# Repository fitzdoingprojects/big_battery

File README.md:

# big_battery
Charge Controller for 12 cell Lifepo4 batteries

Output voltage can be adjusted between 0 and 110% with voltage between TRM and -S on CN1:
Output Voltage = (Voltage between TMR and -S / 2.5) * 5V

Output current can be measured between CB adn -S on either CN1 or CN2.
Ouput current: 1Vcb = 0A, 0Vcb = 50A, -1Vcb = 100A
	Iout = 50 * (-Vcb + 1)
Required input impedance > 500kOh
Max current 120A ???

Circuit:
	Set TRM to default ouput of 4.2V, allow output range of 0 to 4.2V
	Invert and shift current sense from -1 to 2V, to 0V to 2.4V
	Over current feedback, with max current and trickle current
	Isolated signalling, either capacitive or dedicated IC

TESTING:
	* Double check default output voltage of 4.2V
	* Double check current graph/equation

Results:
    With 0 current, CB measuers 1.221V
    1A , 1.5V
    2A, 1.13
	3A, 1.098
	4A, 1.069
	5A, 1.04
SHOULD REQUIRE DIRECT TURN OFF?

BOARD REVISION:
 * ADD 3.3V test point
 * ADD potentiometer for adjusting current and voltage set points
 * change plus and minus inputs on op-amp B (because CB voltage decreases as voltage rises)
 * add reverse input protection diode
 * make sure trickle disable is pulled low
 * add some leds for signalling

 HOW FLASH EFM8 MCU:
 
 https://www.silabs.com/community/mcu/8-bit/knowledge-base.entry.html/2015/06/08/how_to_use_efm8_star-8aHu
 https://www.allaboutcircuits.com/projects/custom-pcb-design-with-an-efm8-microcontroller/

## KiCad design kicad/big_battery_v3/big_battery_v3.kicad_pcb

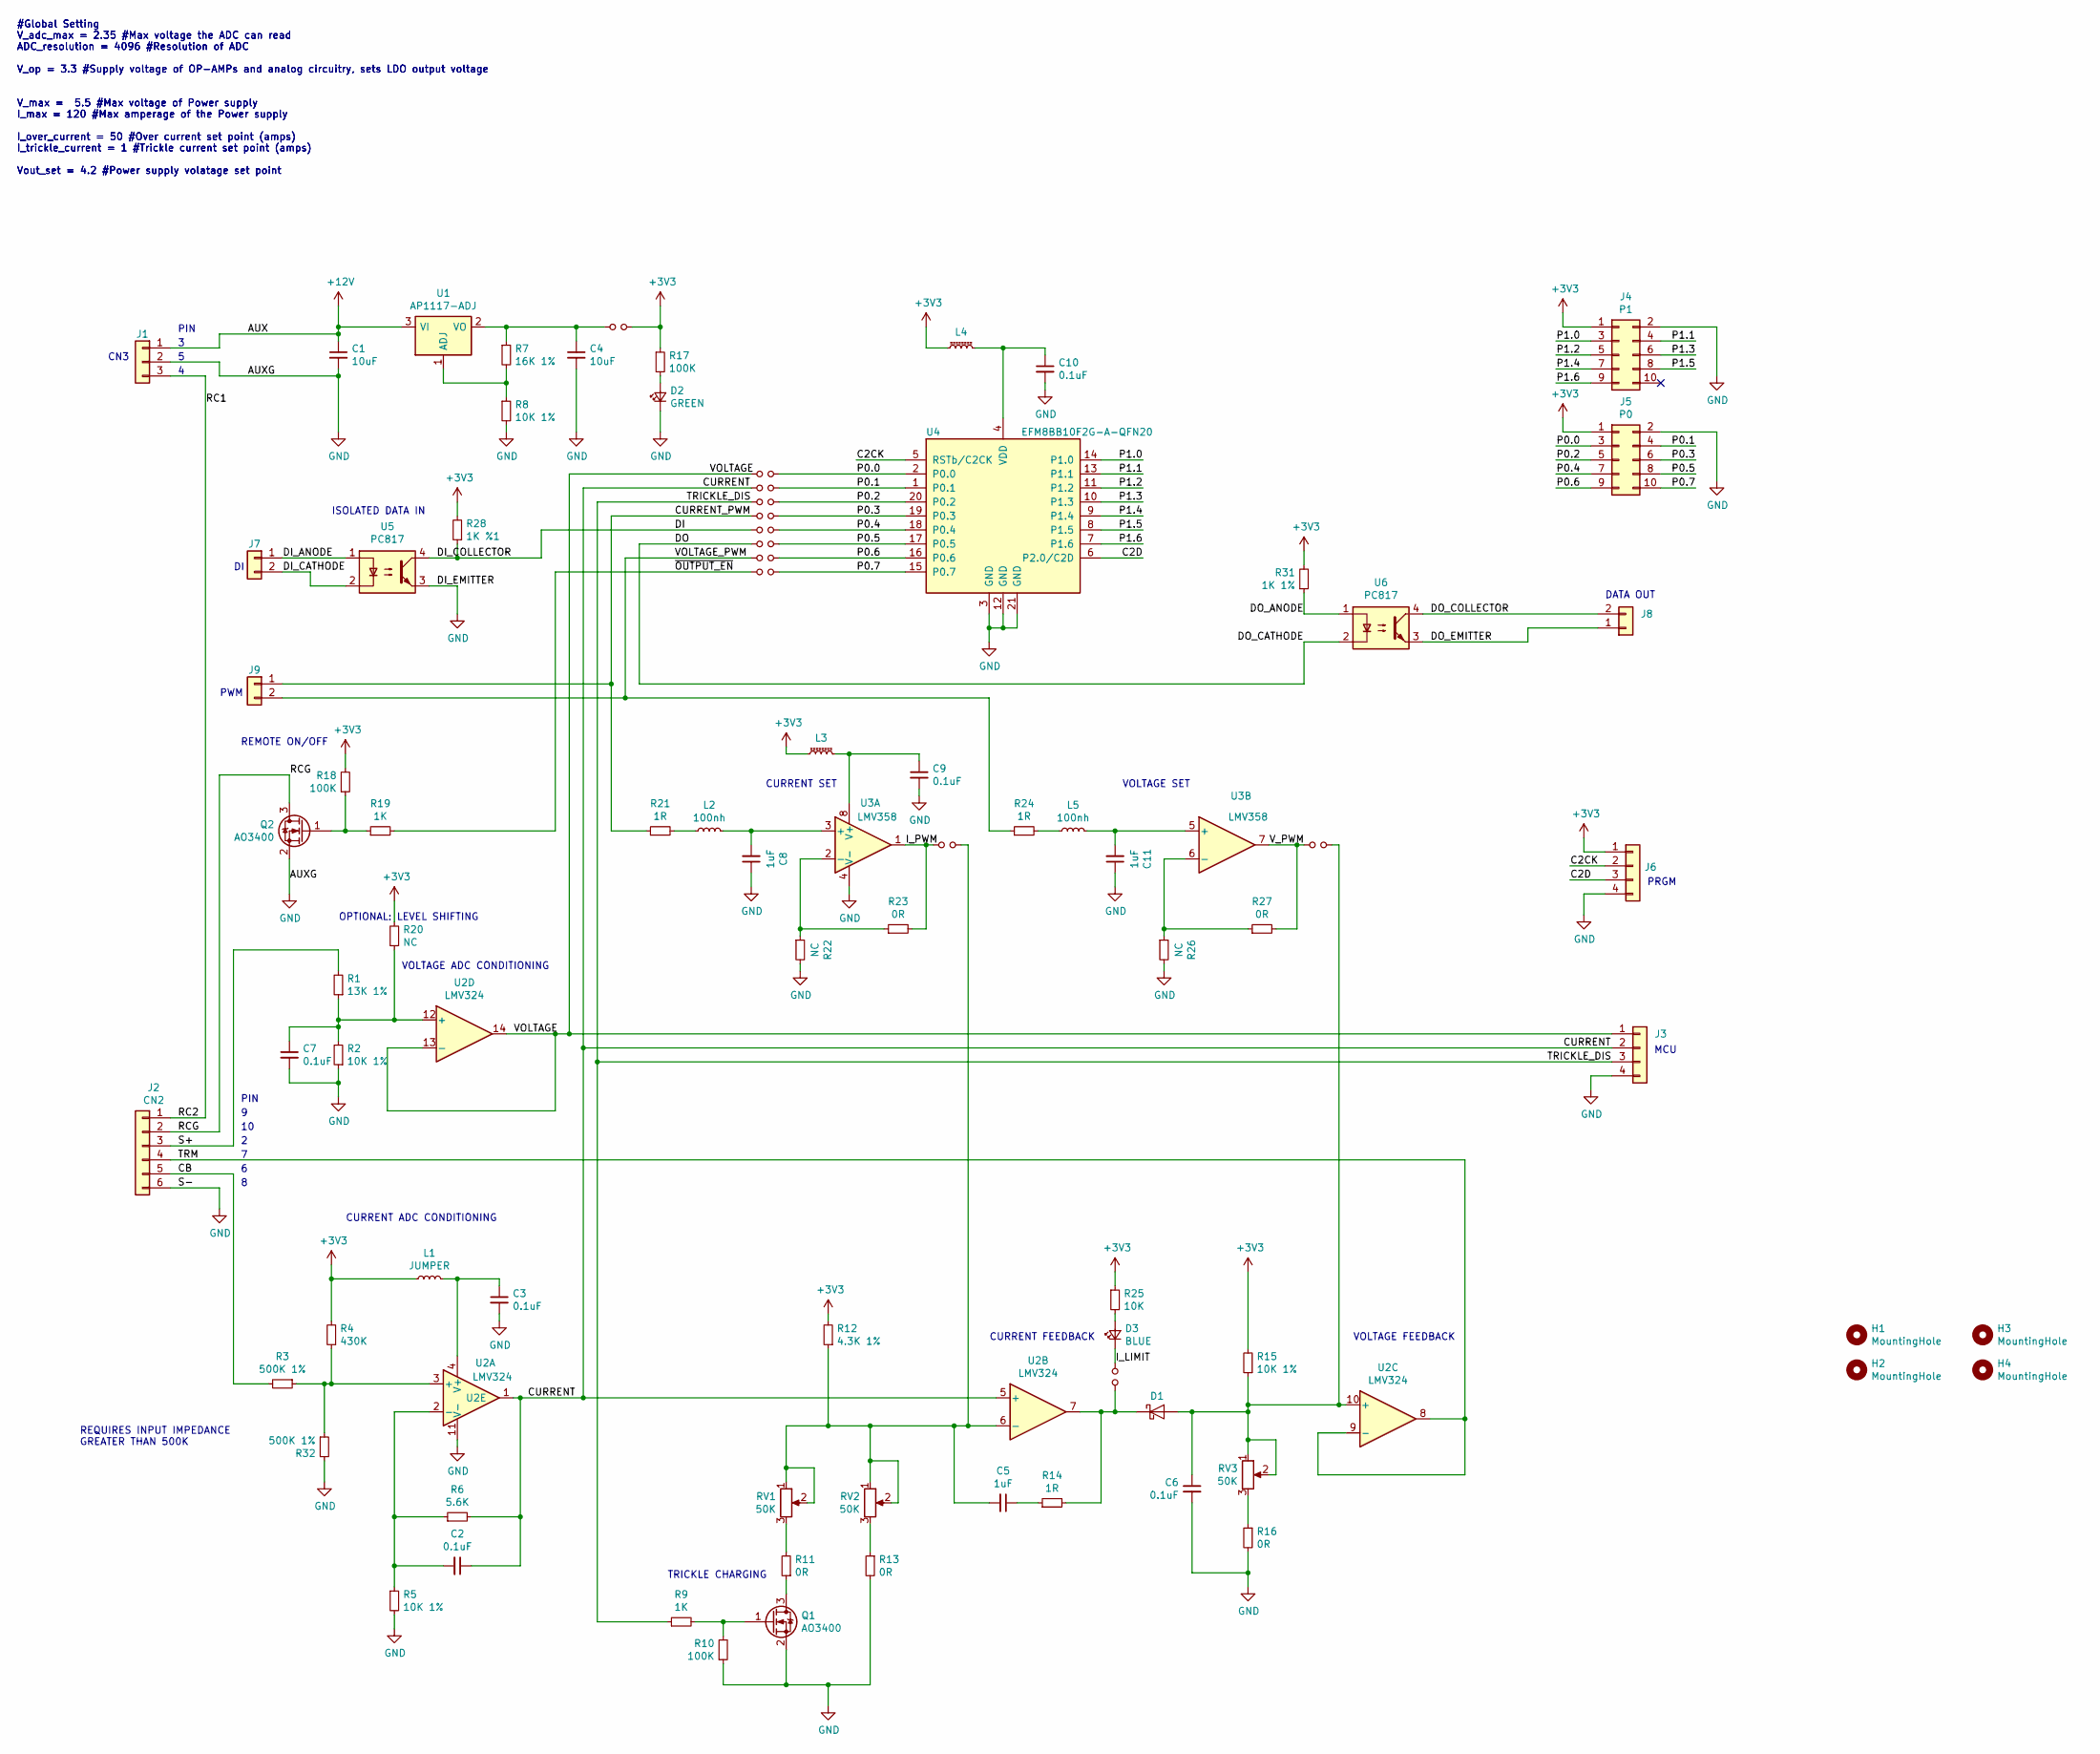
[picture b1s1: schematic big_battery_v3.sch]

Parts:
C1, C4: 10uF; C_0603_1608Metric_Pad1.05x0.95mm_HandSolder
C2, C3, C6, C7, C9, C10: 0.1uF; C_0603_1608Metric_Pad1.05x0.95mm_HandSolder
C5, C8, C11: 1uF; C_0603_1608Metric_Pad1.05x0.95mm_HandSolder
D1: D_Schottky_Small; D_SOD-323_HandSoldering
D2: GREEN; LED_0603_1608Metric_Pad1.05x0.95mm_HandSolder
D3: BLUE; LED_0603_1608Metric_Pad1.05x0.95mm_HandSolder
H1, H2, H3, H4: MountingHole; MountingHole_2.2mm_M2
J1: CONN; JST_EH_B03B-EH-A_1x03_P2.50mm_Vertical
J2: CN2; JST_EH_B06B-EH-A_1x06_P2.50mm_Vertical
J3, J6: CONN; JST_EH_B04B-EH-A_1x04_P2.50mm_Vertical
J4: P1; Multicomp_MC9A12-1034_2x05_P2.54mm_Vertical
J5: P0; Multicomp_MC9A12-1034_2x05_P2.54mm_Vertical
J7, J8, J9: CONN; JST_EH_B02B-EH-A_1x02_P2.50mm_Vertical
JP1, JP2, JP3, JP4, JP5, JP6, JP7, JP8, JP9, JP10, JP11, JP12: Jumper_NO_Small; SolderJumper-2_P1.3mm_Open_RoundedPad1.0x1.5mm
L1: JUMPER; L_0603_1608Metric_Pad1.05x0.95mm_HandSolder
L2, L5: 100nh; L_0603_1608Metric_Pad1.05x0.95mm_HandSolder
L3, L4: L_Core_Ferrite_Small; L_0603_1608Metric_Pad1.05x0.95mm_HandSolder
Q1, Q2: AO3400; SOT-23_Handsoldering
R1: 13K 1%; R_0603_1608Metric_Pad1.05x0.95mm_HandSolder
R2, R5, R8, R15: 10K 1%; R_0603_1608Metric_Pad1.05x0.95mm_HandSolder
R3, R32: 500K 1%; R_0603_1608Metric_Pad1.05x0.95mm_HandSolder
R4: 430K; R_0603_1608Metric_Pad1.05x0.95mm_HandSolder
R6: 5.6K; R_0603_1608Metric_Pad1.05x0.95mm_HandSolder
R7: 16K 1%; R_0603_1608Metric_Pad1.05x0.95mm_HandSolder
R9, R19: 1K; R_0603_1608Metric_Pad1.05x0.95mm_HandSolder
R10, R17, R18: 100K; R_0603_1608Metric_Pad1.05x0.95mm_HandSolder
R11, R13, R16, R23, R27: 0R; R_0603_1608Metric_Pad1.05x0.95mm_HandSolder
R12: 4.3K 1%; R_0603_1608Metric_Pad1.05x0.95mm_HandSolder
R14, R21, R24: 1R; R_0603_1608Metric_Pad1.05x0.95mm_HandSolder
R20, R22, R26: NC; R_0603_1608Metric_Pad1.05x0.95mm_HandSolder
R25: 10K; R_0603_1608Metric_Pad1.05x0.95mm_HandSolder
R28: 1K %1; R_0603_1608Metric_Pad1.05x0.95mm_HandSolder
R31: 1K 1%; R_0603_1608Metric_Pad1.05x0.95mm_HandSolder
RV1, RV2, RV3: 50K; Potentiometer_Bourns_3296W_Vertical
U1: AP1117-ADJ; SOT-223-3_TabPin2
U2: LMV324; SOIC-14_3.9x8.7mm_P1.27mm
U3: LMV358; SOIC-8_3.9x4.9mm_P1.27mm
U4: EFM8BB10F2G-A-QFN20; SiliconLabs_QFN-20-1EP_3x3mm_P0.5mm_ThermalVias
U5, U6: PC817; DIP-4_W7.62mm

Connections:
+3V3: J4.1, J5.1, J6.1, JP1.2, L1.1, L3.1, L4.1, R4.2, R12.2, R15.2, R17.1, R18.2, R20.2, R25.1, R28.2, R31.2
+12V: C1.1, J1.1, U1.3 (VI)
/C2CK: J6.2, U4.5 (RSTb/C2CK)
/C2D: J6.3, U4.6 (P2.0/C2D)
/CB: J2.5, R3.2
/CURRENT: C2.1, J3.2, JP3.1, R6.2, U2.1, U2.5 (+)
/CURRENT_PWM: J9.1, JP5.1, R21.1
/DI: JP6.1, R28.1, U5.4
/DI_ANODE: J7.1, U5.1
/DI_CATHODE: J7.2, U5.2
/DO: JP7.1, U6.2
/DO_ANODE: R31.1, U6.1
/DO_COLLECTOR: J8.2, U6.4
/DO_EMITTER: J8.1, U6.3
/I_LIMIT: D3.1 (K), JP9.2
/I_PWM: JP8.1, R23.2, U3.1
/P0.0: J5.3, JP2.2, U4.2 (P0.0)
/P0.1: J5.4, JP3.2, U4.1 (P0.1)
/P0.2: J5.5, JP4.2, U4.20 (P0.2)
/P0.3: J5.6, JP5.2, U4.19 (P0.3)
/P0.4: J5.7, JP6.2, U4.18 (P0.4)
/P0.5: J5.8, JP7.2, U4.17 (P0.5)
/P0.6: J5.9, JP11.2, U4.16 (P0.6)
/P0.7: J5.10, JP12.2, U4.15 (P0.7)
/P1.0: J4.3, U4.14 (P1.0)
/P1.1: J4.4, U4.13 (P1.1)
/P1.2: J4.5, U4.11 (P1.2)
/P1.3: J4.6, U4.10 (P1.3)
/P1.4: J4.7, U4.9 (P1.4)
/P1.5: J4.8, U4.8 (P1.5)
/P1.6: J4.9, U4.7 (P1.6)
/RC1: J1.3, J2.1
/RCG: J2.2, Q2.3 (D)
/S+: J2.3, R1.2
/TRICKLE_DIS: J3.3, JP4.1, R9.1
/TRM: J2.4, U2.8, U2.9 (-)
/VOLTAGE: J3.1, JP2.1, U2.13 (-), U2.14
/VOLTAGE_PWM: J9.2, JP11.1, R24.1
/V_PWM: JP10.1, R27.2, U3.7
/~OUTPUT_EN: JP12.1, R19.2
GND: C1.2, C3.2, C4.2, C6.2, C7.2, C8.1, C9.2, C10.2, C11.1, D2.1 (K), J1.2, J2.6, J3.4, J4.2, J5.2, J6.4, Q1.2 (S), Q2.2 (S), R2.1, R5.2, R8.2, R10.1, R13.2, R16.2, R22.2, R26.2, R32.2, U2.11 (V-), U3.4 (V-), U4.3 (GND), U4.12 (GND), U4.21 (GND), U5.3
unnamed: C2.2, R5.1, R6.1, U2.2 (-)
unnamed: C3.1, L1.2, U2.4 (V+)
unnamed: C4.1, JP1.1, R7.1, U1.2 (VO)
unnamed: C5.1, R14.1
unnamed: C5.2, JP8.2, R12.1, RV1.1, RV1.2, RV2.1, RV2.2, U2.6 (-)
unnamed: C6.1, D1.2 (A), JP10.2, R15.1, RV3.1, RV3.2, U2.10 (+)
unnamed: C7.1, R1.1, R2.2, R20.1, U2.12 (+)
unnamed: C8.2, L2.2, U3.3 (+)
unnamed: C9.1, L3.2, U3.8 (V+)
unnamed: C10.1, L4.2, U4.4 (VDD)
unnamed: C11.2, L5.2, U3.5 (+)
unnamed: D1.1 (K), JP9.1, R14.2, U2.7
unnamed: D2.2 (A), R17.2
unnamed: D3.2 (A), R25.2
unnamed: L2.1, R21.2
unnamed: L5.1, R24.2
unnamed: Q1.1 (G), R9.2, R10.2
unnamed: Q1.3 (D), R11.1
unnamed: Q2.1 (G), R18.1, R19.1
unnamed: R3.1, R4.1, R32.1, U2.3 (+)
unnamed: R7.2, R8.1, U1.1 (ADJ)
unnamed: R11.2, RV1.3
unnamed: R13.1, RV2.3
unnamed: R16.1, RV3.3
unnamed: R22.1, R23.1, U3.2 (-)
unnamed: R26.1, R27.1, U3.6 (-)

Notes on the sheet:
REQUIRES INPUT IMPEDANCE GREATER THAN 500K
#Global Setting V_adc_max = 2.35 #Max voltage the ADC can read ADC_resolution = 4096 #Resolution of ADC V_op = 3.3 #Supply voltage of OP-AMPs and analog circuitry, sets LDO output voltage V_max = 5.5 #Max voltage of Power supply I_max = 120 #Max amperage of the Power supply I_over_current = 50 #Ove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
OPTIONAL: LEVEL SHIFTING
CURRENT SET
VOLTAGE SET
VOLTAGE ADC CONDITIONING
CURRENT ADC CONDITIONING
CURRENT FEEDBACK
VOLTAGE FEEDBACK
TRICKLE CHARGING
ISOLATED DATA IN
REMOTE ON/OFF
PIN
DATA OUT
CN3
PWM
PRGM
MCU

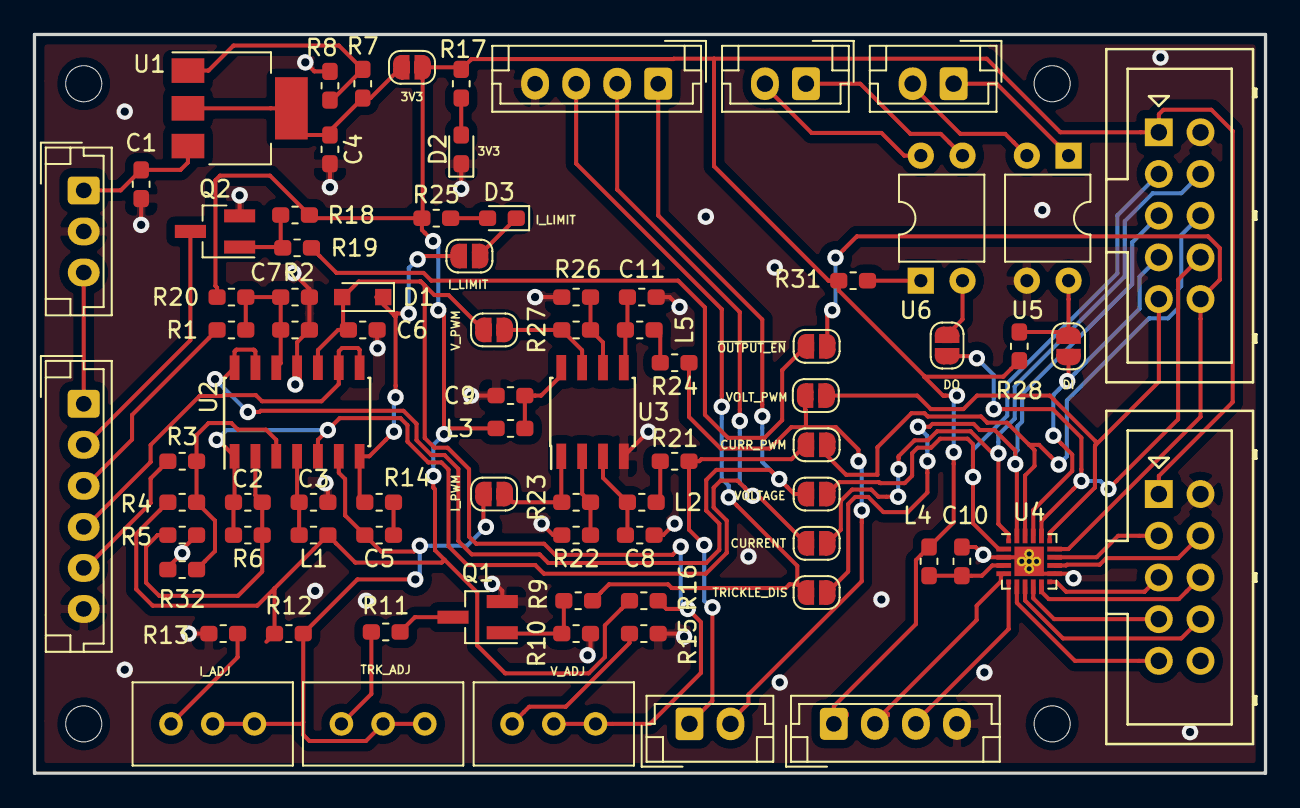
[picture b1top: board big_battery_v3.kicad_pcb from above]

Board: 2 copper layers, 75.0 x 45.0 mm, 85 parts (0 on the bottom side), 67 nets.

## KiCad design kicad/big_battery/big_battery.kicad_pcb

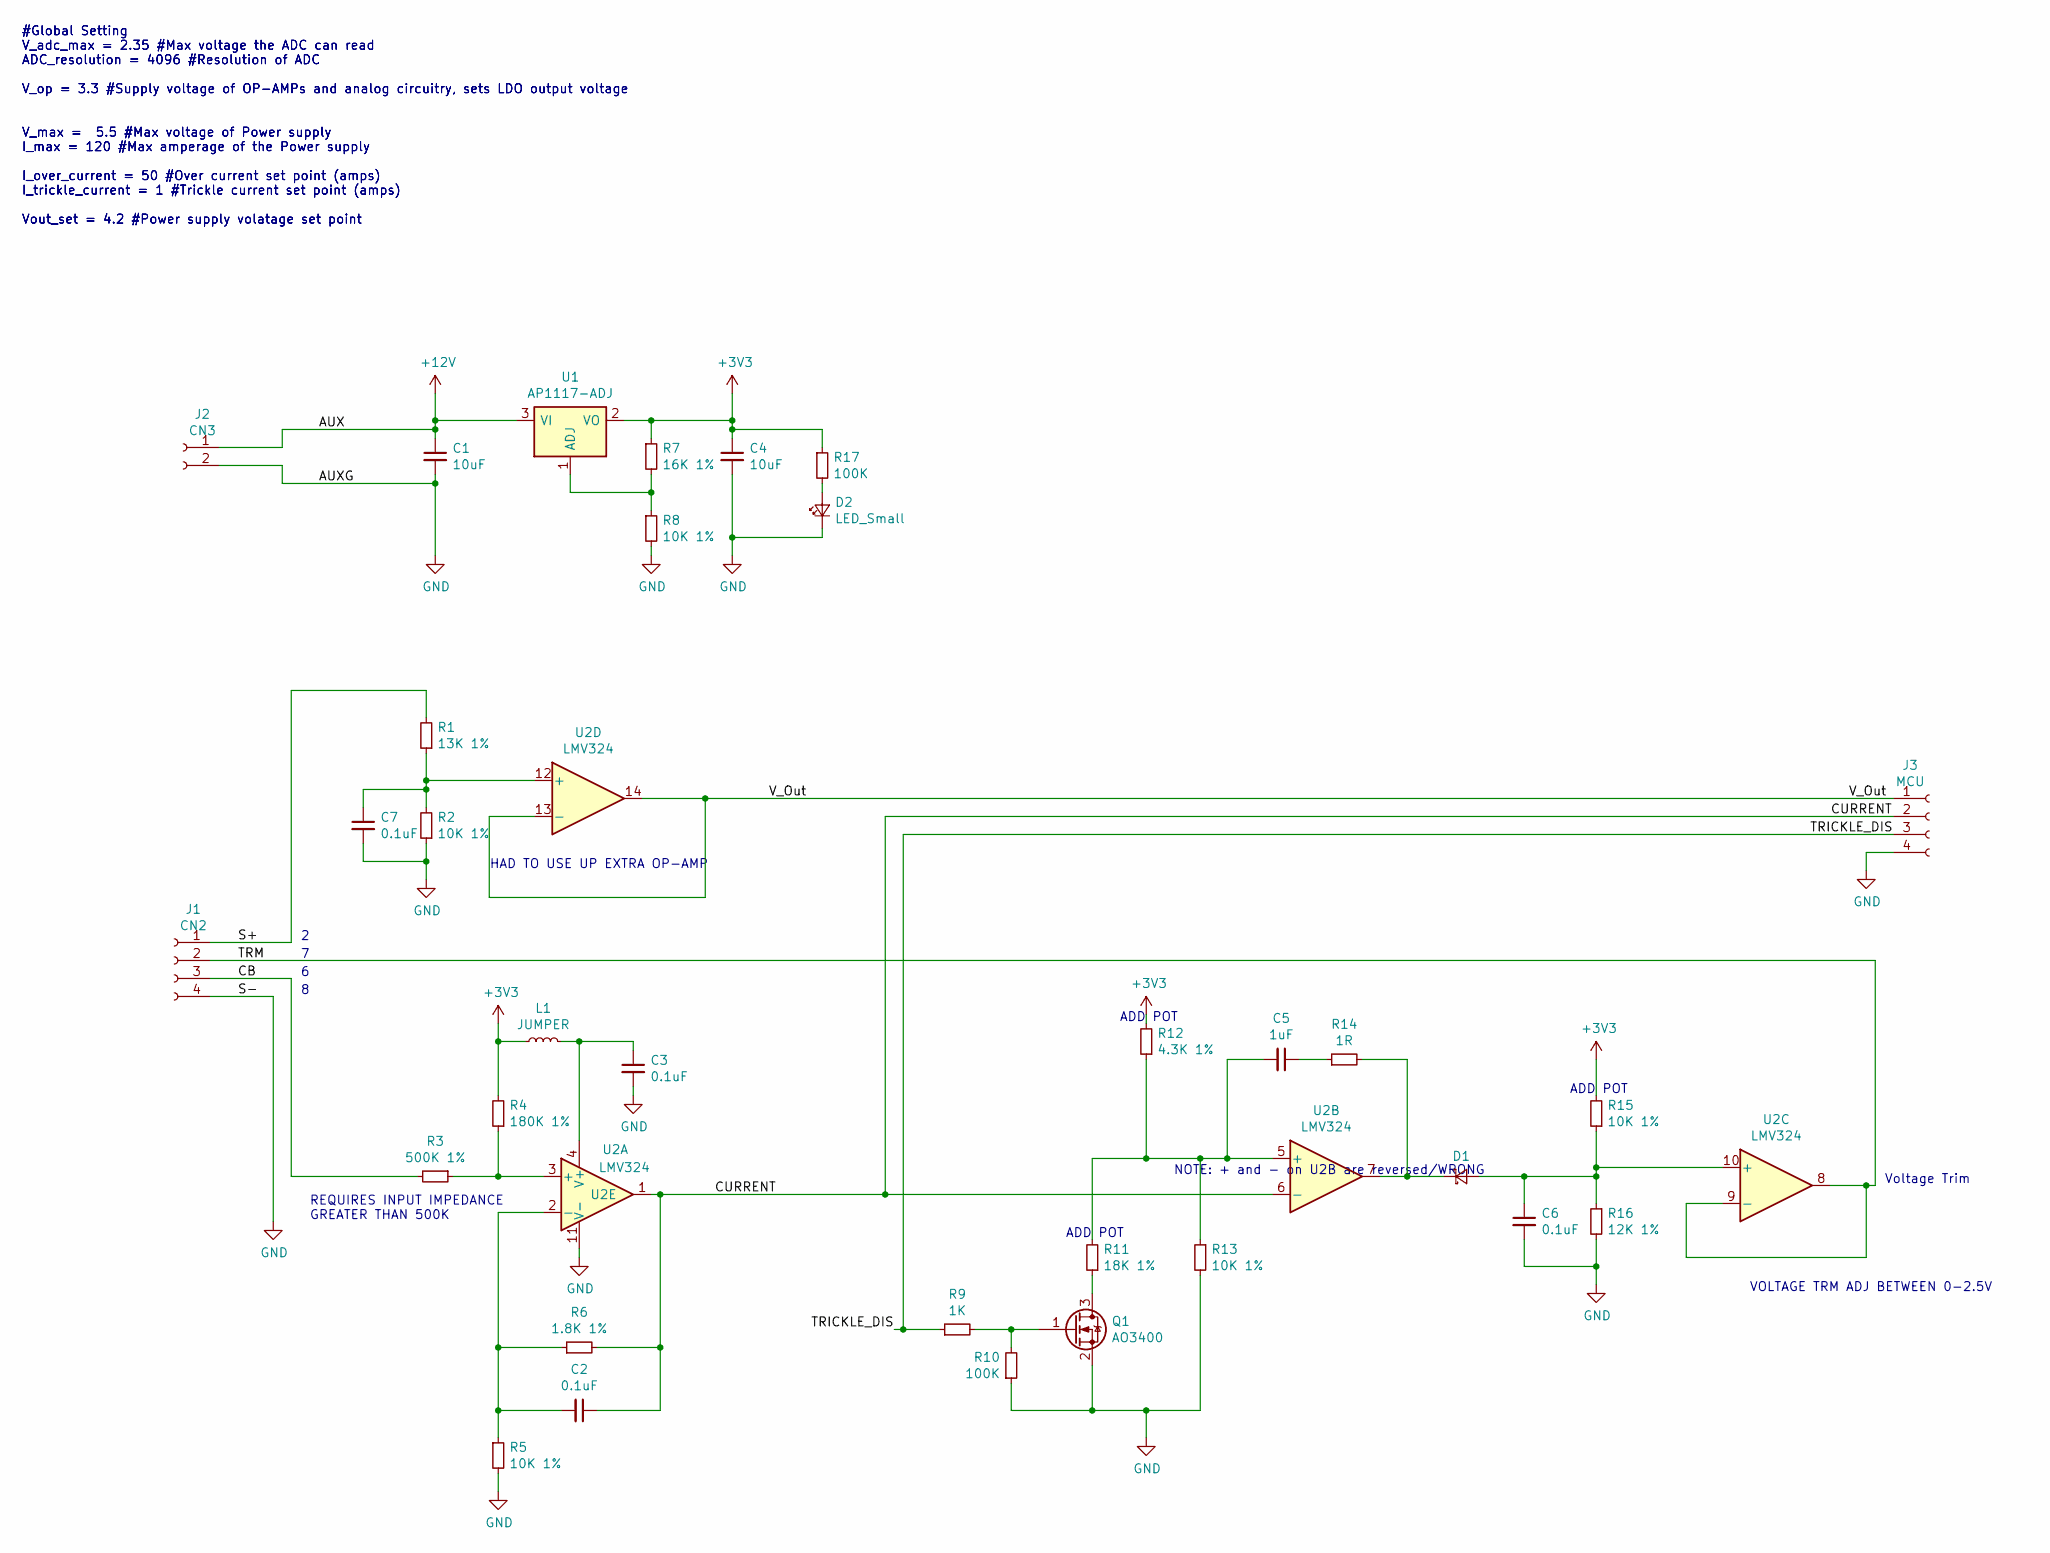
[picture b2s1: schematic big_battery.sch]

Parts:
C1, C4: 10uF; C_0603_1608Metric_Pad1.05x0.95mm_HandSolder
C2, C3, C6, C7: 0.1uF; C_0603_1608Metric_Pad1.05x0.95mm_HandSolder
C5: 1uF; C_0603_1608Metric_Pad1.05x0.95mm_HandSolder
D1: D_Schottky_Small; D_0603_1608Metric_Castellated
D2: LED_Small
J1: CN2; PinSocket_1x04_P2.54mm_Vertical
J2: CN3; PinSocket_1x02_P2.54mm_Vertical
J3: MCU; PinSocket_1x04_P2.54mm_Vertical
L1: JUMPER; L_0603_1608Metric_Pad1.05x0.95mm_HandSolder
Q1: AO3400; SOT-23_Handsoldering
R1: 13K 1%; R_0603_1608Metric_Pad1.05x0.95mm_HandSolder
R2, R5, R8, R13, R15: 10K 1%; R_0603_1608Metric_Pad1.05x0.95mm_HandSolder
R3: 500K 1%; R_0603_1608Metric_Pad1.05x0.95mm_HandSolder
R4: 180K 1%; R_0603_1608Metric_Pad1.05x0.95mm_HandSolder
R6: 1.8K 1%; R_0603_1608Metric_Pad1.05x0.95mm_HandSolder
R7: 16K 1%; R_0603_1608Metric_Pad1.05x0.95mm_HandSolder
R9: 1K; R_0603_1608Metric_Pad1.05x0.95mm_HandSolder
R10, R17: 100K; R_0603_1608Metric_Pad1.05x0.95mm_HandSolder
R11: 18K 1%; R_0603_1608Metric_Pad1.05x0.95mm_HandSolder
R12: 4.3K 1%; R_0603_1608Metric_Pad1.05x0.95mm_HandSolder
R14: 1R; R_0603_1608Metric_Pad1.05x0.95mm_HandSolder
R16: 12K 1%; R_0603_1608Metric_Pad1.05x0.95mm_HandSolder
U1: AP1117-ADJ; SOT-223-3_TabPin2
U2: LMV324; SOIC-14_3.9x8.7mm_P1.27mm

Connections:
+3V3: C4.1, L1.1, R4.2, R7.1, R12.2, R15.2, R17.1, U1.2 (VO)
+12V: C1.1, J2.1, U1.3 (VI)
/CB: J1.3, R3.2
/CURRENT: C2.1, J3.2, R6.2, U2.1, U2.6 (-)
/S+: J1.1, R1.2
/TRICKLE_DIS: J3.3, R9.1
/TRM: J1.2, U2.8, U2.9 (-)
/V_Out: J3.1, U2.13 (-), U2.14
GND: C1.2, C3.2, C4.2, C6.2, C7.2, D2.1 (K), J1.4, J2.2, J3.4, Q1.2 (S), R2.1, R5.2, R8.2, R10.1, R13.2, R16.2, U2.11 (V-)
unnamed: C2.2, R5.1, R6.1, U2.2 (-)
unnamed: C3.1, L1.2, U2.4 (V+)
unnamed: C5.1, R14.1
unnamed: C5.2, R11.2, R12.1, R13.1, U2.5 (+)
unnamed: C6.1, D1.2 (A), R15.1, R16.1, U2.10 (+)
unnamed: C7.1, R1.1, R2.2, U2.12 (+)
unnamed: D1.1 (K), R14.2, U2.7
unnamed: D2.2 (A), R17.2
unnamed: Q1.1 (G), R9.2, R10.2
unnamed: Q1.3 (D), R11.1
unnamed: R3.1, R4.1, U2.3 (+)
unnamed: R7.2, R8.1, U1.1 (ADJ)

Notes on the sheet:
HAD TO USE UP EXTRA OP-AMP
REQUIRES INPUT IMPEDANCE GREATER THAN 500K
VOLTAGE TRM ADJ BETWEEN 0-2.5V
Voltage Trim
#Global Setting V_adc_max = 2.35 #Max voltage the ADC can read ADC_resolution = 4096 #Resolution of ADC V_op = 3.3 #Supply voltage of OP-AMPs and analog circuitry, sets LDO output voltage V_max = 5.5 #Max voltage of Power supply I_max = 120 #Max amperage of the Power supply I_over_current = 50 #Ove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
NOTE: + and - on U2B are reversed/WRONG
ADD POT

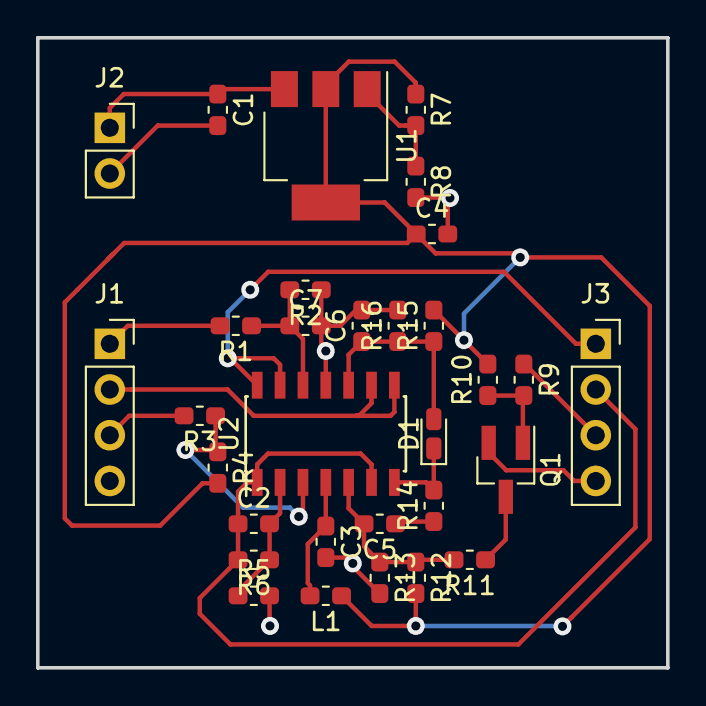
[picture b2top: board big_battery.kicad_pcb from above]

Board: 2 copper layers, 35.0 x 35.0 mm, 31 parts (0 on the bottom side), 20 nets.

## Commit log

2018-10-27 mech, schematic, script for component values, and datasheet
2018-10-30 fixes component selection script
2018-11-14 pretty much working board, requires some bodges on the op-amp and extra potentiometers
2018-11-14 adds library schematic rescue .dcm file
2018-11-14 attempt to fix kicad symbol library
2018-11-22 adds big battery v2.0
2018-11-23 fixing up silkscreen
2018-11-28 final gerbers sent out
2018-11-28 adds gerbers and rescue libs
2018-12-11 adds first firmware version
2018-12-11 got uart working
2018-12-12 got pwm working
2018-12-12 got gpio working
2018-12-19 got most of uart communication working
2018-12-19 tested rest of uart communication
2018-12-19 updated schematic to include bodge wires
2019-02-06 made a gui interface
2019-02-07 saving workingish serial communication before rewrite
2019-02-07 cleans up communication gui code
2019-04-24 adds big battery v3
2020-02-26 updates interactive bom for big_battery3
